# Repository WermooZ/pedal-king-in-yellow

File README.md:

# pedal-king-in-yellow

<br />This work is licensed under a <a rel="license" href="http://creativecommons.org/licenses/by-nc-sa/4.0/">Creative Commons Attribution-NonCommercial-ShareAlike 4.0 International License</a>.

Based on the **Exar Super Fuzz SF-02** traced by **VitaliiBobrov** at www.freestompboxes.org

https://www.freestompboxes.org/viewtopic.php?p=293456&hilit=exar#p293456

SF-2 is a fuzz pedal, handmade in Poland in 90s by not existing now Exar Electronix (Janusz Raczyk and Leszek Gruszka).

This version is modified a bit to my taste to improve clarity, tone and noise levels.

Project was assembled and tested - only thing that I messed up is a dual FREQ pot pins -> they are mirrored for one half of pot but it can be fixed by correct wiring so check the schematic first.

Please use Pieczarka logo on pedal enclosure if you want to design own graphics or 'Pieczarka' or 'PCZR' for short.

Project thread on FSB: https://www.freestompboxes.org/viewtopic.php?t=32591

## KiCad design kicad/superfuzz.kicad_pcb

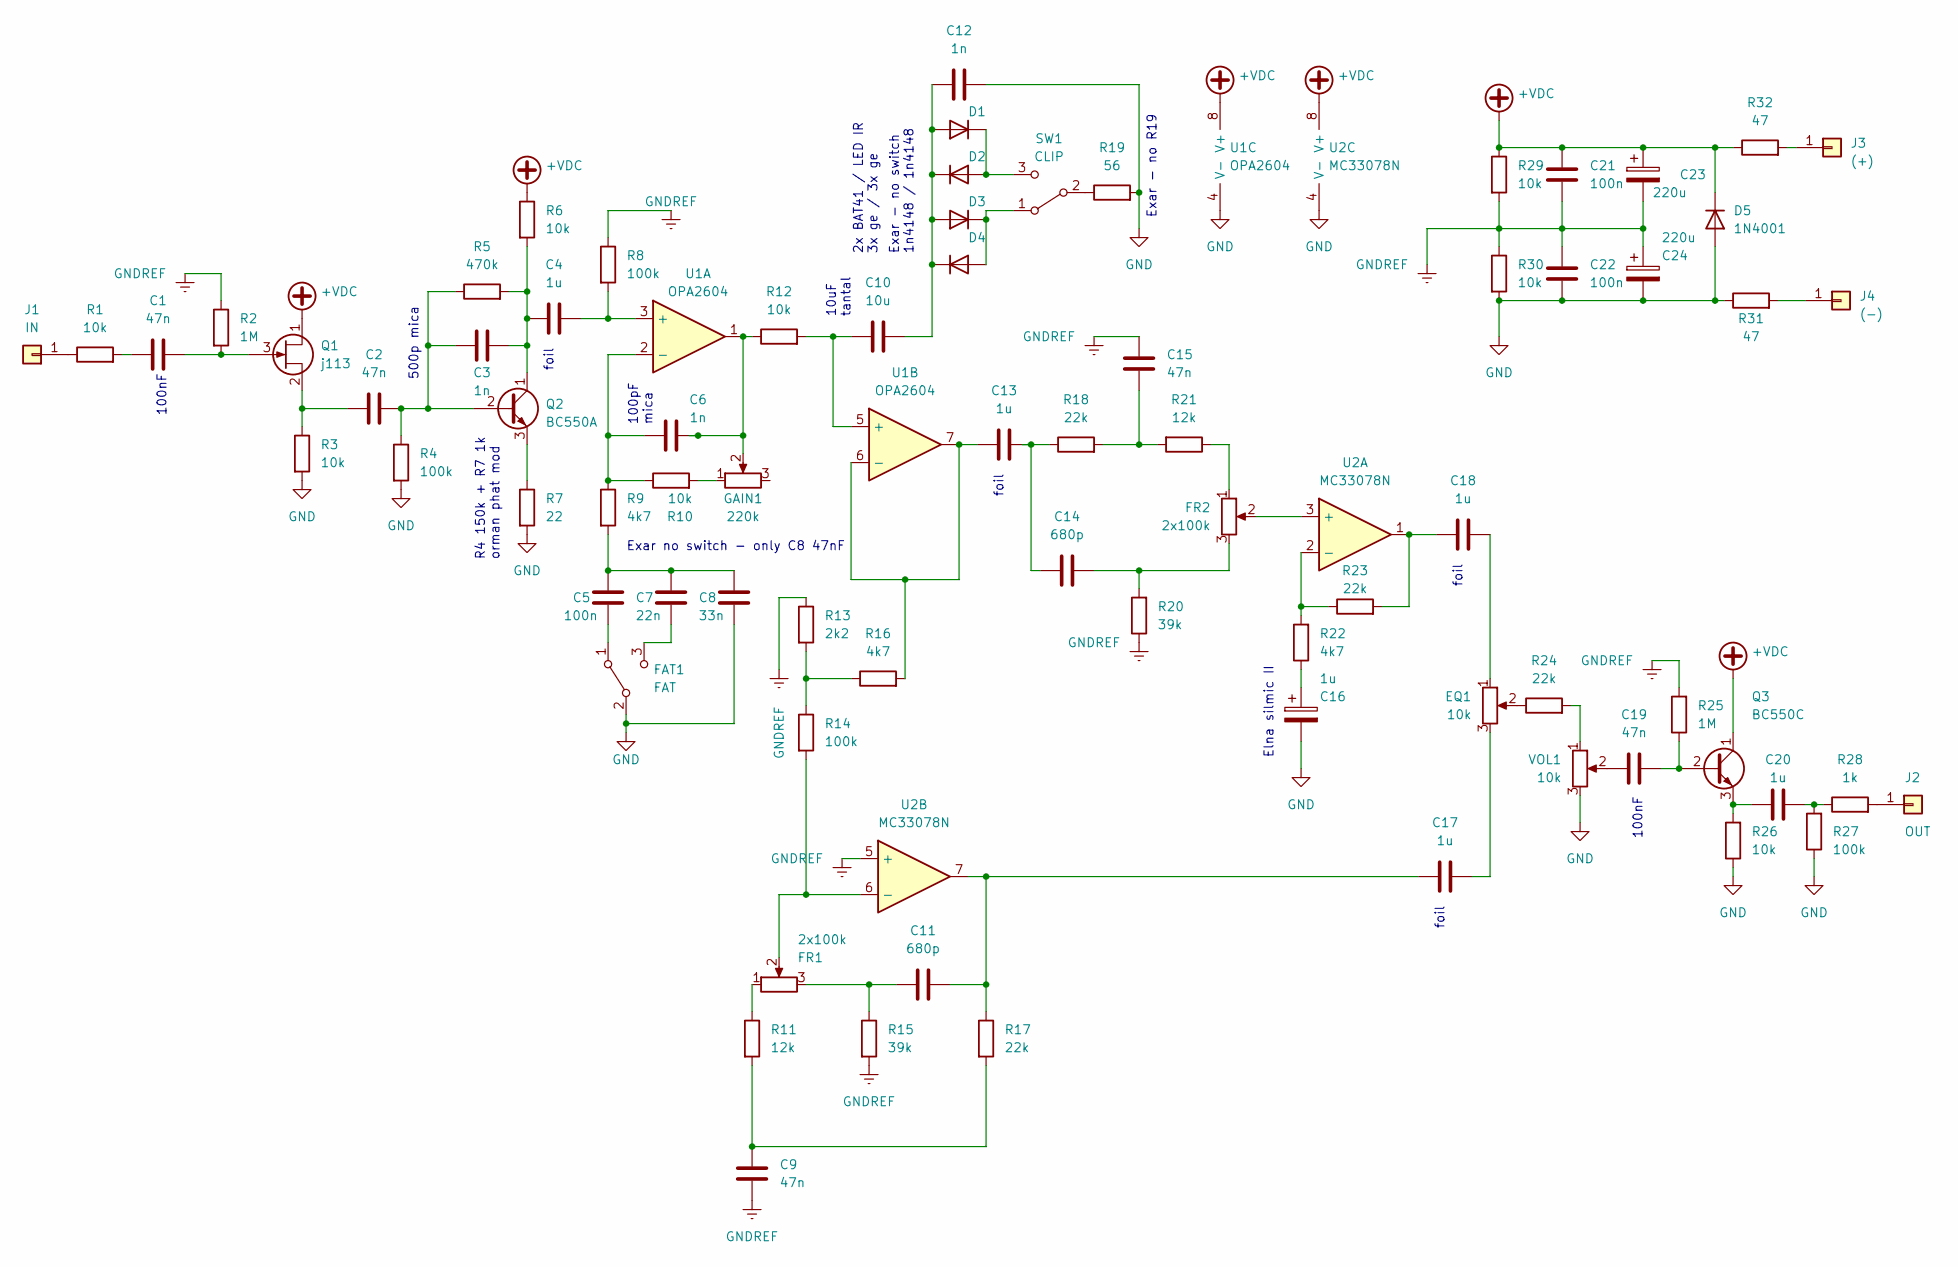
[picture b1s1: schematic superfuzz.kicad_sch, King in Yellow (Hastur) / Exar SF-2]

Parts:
C1, C2, C9, C15, C19: 47n; C_Rect_L13.0mm_W5.0mm_P10.00mm_FKS3_FKP3_MKS4
C3, C6, C12: 1n; C_Rect_L10.0mm_W5.0mm_P5.00mm_P7.50mm
C4, C13, C17, C18, C20: 1u; C_Rect_L7.2mm_W8.5mm_P5.00mm_FKP2_FKP2_MKS2_MKP2
C5: 100n; C_Rect_L10.0mm_W4.0mm_P7.50mm_MKS4
C7: 22n; C_Rect_L10.0mm_W4.0mm_P7.50mm_MKS4
C8: 33n; C_Rect_L10.0mm_W4.0mm_P7.50mm_MKS4
C10: 10u; C_Rect_L7.2mm_W8.5mm_P5.00mm_FKP2_FKP2_MKS2_MKP2
C11, C14: 680p; C_Rect_L7.2mm_W5.5mm_P5.00mm_FKS2_FKP2_MKS2_MKP2
C16: 1u; CP_Radial_D5.0mm_P2.50mm
C21, C22: 100n; C_Rect_L7.2mm_W5.5mm_P5.00mm_FKS2_FKP2_MKS2_MKP2
C23, C24: 220u; CP_Radial_D8.0mm_P5.00mm
D1, D2: 1N4148; D_DO-35_SOD27_P2.54mm_Vertical_AnodeUp
D3, D4: Ge; D_DO-35_SOD27_P2.54mm_Vertical_AnodeUp
D5: 1N4001; D_DO-41_SOD81_P3.81mm_Vertical_AnodeUp
EQ1: 10k; potek2
FAT1: FAT; potek2
FR1, FR2: 2x100k; potek2
GAIN1: 220k; potek2
J1: IN; Pin_D0.7mm_L6.5mm_W1.8mm_FlatFork
J2: OUT; Pin_D0.7mm_L6.5mm_W1.8mm_FlatFork
J3: (+); Pin_D0.7mm_L6.5mm_W1.8mm_FlatFork
J4: (-); Pin_D0.7mm_L6.5mm_W1.8mm_FlatFork
Q1: j113; TO-92_Inline_Wide
Q2: BC550A; TO-92_Inline
Q3: BC550C; TO-92_Inline
R1, R12, R26, R30: 10k; R_Axial_DIN0204_L3.6mm_D1.6mm_P2.54mm_Vertical
R2, R25: 1M; R_Axial_DIN0204_L3.6mm_D1.6mm_P7.62mm_Horizontal
R3, R6, R10, R29: 10k; R_Axial_DIN0204_L3.6mm_D1.6mm_P5.08mm_Horizontal
R4, R27: 100k; R_Axial_DIN0204_L3.6mm_D1.6mm_P5.08mm_Horizontal
R5: 470k; R_Axial_DIN0204_L3.6mm_D1.6mm_P5.08mm_Horizontal
R7: 22; R_Axial_DIN0204_L3.6mm_D1.6mm_P5.08mm_Horizontal
R8: 100k; R_Axial_DIN0204_L3.6mm_D1.6mm_P7.62mm_Horizontal
R9: 4k7; R_Axial_DIN0204_L3.6mm_D1.6mm_P5.08mm_Horizontal
R11: 12k; R_Axial_DIN0204_L3.6mm_D1.6mm_P5.08mm_Horizontal
R13: 2k2; R_Axial_DIN0204_L3.6mm_D1.6mm_P2.54mm_Vertical
R14: 100k; R_Axial_DIN0204_L3.6mm_D1.6mm_P2.54mm_Vertical
R15: 39k; R_Axial_DIN0204_L3.6mm_D1.6mm_P2.54mm_Vertical
R16, R22: 4k7; R_Axial_DIN0204_L3.6mm_D1.6mm_P2.54mm_Vertical
R17: 22k; R_Axial_DIN0204_L3.6mm_D1.6mm_P5.08mm_Horizontal
R18, R23, R24: 22k; R_Axial_DIN0204_L3.6mm_D1.6mm_P2.54mm_Vertical
R19: 56; R_Axial_DIN0204_L3.6mm_D1.6mm_P2.54mm_Vertical
R20: 39k; R_Axial_DIN0204_L3.6mm_D1.6mm_P5.08mm_Horizontal
R21: 12k; R_Axial_DIN0204_L3.6mm_D1.6mm_P2.54mm_Vertical
R28: 1k; R_Axial_DIN0204_L3.6mm_D1.6mm_P5.08mm_Horizontal
R31, R32: 47; R_Axial_DIN0204_L3.6mm_D1.6mm_P2.54mm_Vertical
SW1: CLIP; potek2
U1: OPA2604; DIP-8_W7.62mm_LongPads
U2: MC33078N; DIP-8_W7.62mm_LongPads
VOL1: 10k; potek2

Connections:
+VDC: C21.1, C23.1, D5.1 (K), Q1.1 (D), Q3.1 (C), R6.1, R29.1, R32.1, U1.8 (V+), U2.8 (V+)
GND: C8.2, C12.2, C16.2, C22.2, C24.2, D5.2 (A), FAT1.2 (B), R3.2, R4.2, R7.2, R19.2, R26.1, R27.1, R30.2, R31.1, U1.4 (V-), U2.4 (V-), VOL1.3
GNDREF: C9.1, C15.2, C21.2, C22.1, C23.2, C24.1, R2.1, R8.1, R13.1, R15.2, R20.1, R25.2, R29.2, R30.1, U2.5 (+)
unnamed: C1.1, R1.2
unnamed: C1.2, Q1.3 (G), R2.2
unnamed: C2.1, Q1.2 (S), R3.1
unnamed: C2.2, C3.1, Q2.2 (B), R4.1, R5.1
unnamed: C3.2, C4.1, Q2.1 (C), R5.2, R6.2
unnamed: C4.2, R8.2, U1.3 (+)
unnamed: C5.1, C7.1, C8.1, R9.2
unnamed: C5.2, FAT1.1 (A)
unnamed: C6.1, R9.1, R10.1, U1.2 (-)
unnamed: C6.2, GAIN1.2, R12.1, U1.1
unnamed: C7.2, FAT1.3 (C)
unnamed: C9.2, R11.2, R17.2
unnamed: C10.1, R12.2, U1.5 (+)
unnamed: C10.2, C12.1, D1.2 (A), D2.1 (K), D3.2 (A), D4.1 (K)
unnamed: C11.1, FR1.3, R15.1
unnamed: C11.2, C17.1, R17.1, U2.7
unnamed: C13.1, R16.2, U1.6 (-), U1.7
unnamed: C13.2, C14.1, R18.1
unnamed: C14.2, FR2.3, R20.2
unnamed: C15.1, R18.2, R21.2
unnamed: C16.1, R22.1
unnamed: C17.2, EQ1.3
unnamed: C18.1, R23.2, U2.1
unnamed: C18.2, EQ1.1
unnamed: C19.1, VOL1.2
unnamed: C19.2, Q3.2 (B), R25.1
unnamed: C20.1, Q3.3 (E), R26.2
unnamed: C20.2, R27.2, R28.1
unnamed: D1.1 (K), D2.2 (A), SW1.3 (C)
unnamed: D3.1 (K), D4.2 (A), SW1.1 (A)
unnamed: EQ1.2, R24.1
unnamed: FR1.1, R11.1
unnamed: FR1.2, R14.2, U2.6 (-)
unnamed: FR2.1, R21.1
unnamed: FR2.2, U2.3 (+)
unnamed: GAIN1.1, R10.2
unnamed: J1.1, R1.1
unnamed: J2.1, R28.2
unnamed: J3.1, R32.2
unnamed: J4.1, R31.2
unnamed: Q2.3 (E), R7.1
unnamed: R13.2, R14.1, R16.1
unnamed: R19.1, SW1.2 (B)
unnamed: R22.2, R23.1, U2.2 (-)
unnamed: R24.2, VOL1.1

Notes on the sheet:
Exar - no switch 1n4148 / 1n4148
100nF
Exar no switch - only C8 47nF
500p mica
foil
10uF tantal
Elna silmic II
Exar - no R19
100pF mica
R4 150k + R7 1k orman phat mod
2x BAT41 / LED IR 3x ge / 3x ge

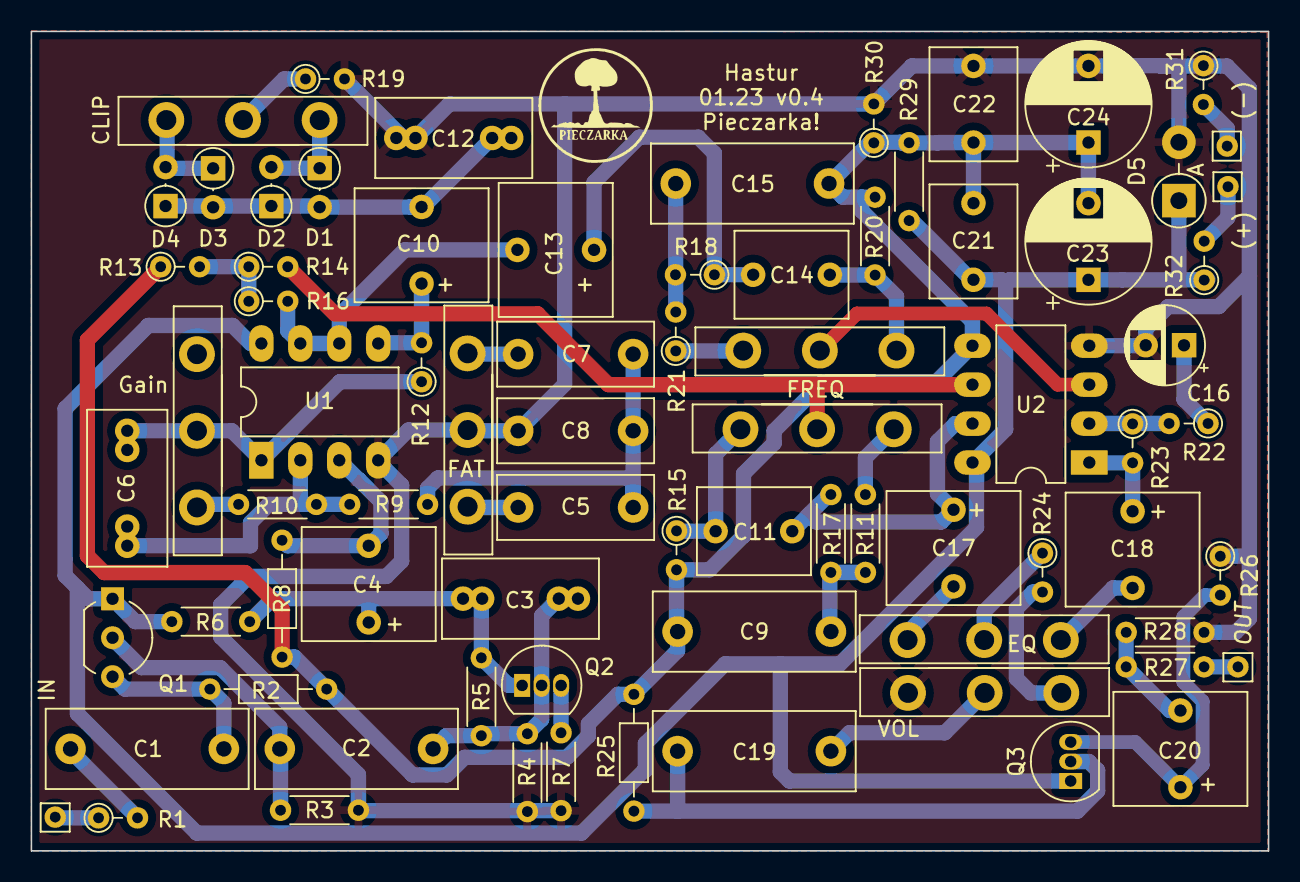
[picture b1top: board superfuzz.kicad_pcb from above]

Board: 2 copper layers, 80.7 x 53.5 mm, 77 parts (0 on the bottom side), 48 nets.

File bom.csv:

Source:,,,,,,
Date:,"sob, 28 sty 2023, 21:35:09",,,,,
Tool:,Eeschema (6.0.10),,,,,
Generator:,/usr/share/kicad/plugins/bom_csv_grouped_by_value_with_fp.py,,,,,
Component Count:,77,,,,,
Ref,Qnty,Value,Cmp name,Footprint,Description,Vendor
"C1, C2, C9, C15, C19, ",5,47n,C,Capacitor_THT:C_Rect_L13.0mm_W5.0mm_P10.00mm_FKS3_FKP3_MKS4,Unpolarized capacitor,
"C3, C6, C12, ",3,1n,C,Capacitor_THT:C_Rect_L10.0mm_W5.0mm_P5.00mm_P7.50mm,Unpolarized capacitor,
"C4, C13, C17, C18, C20, ",5,1u,C,Capacitor_THT:C_Rect_L7.2mm_W8.5mm_P5.00mm_FKP2_FKP2_MKS2_MKP2,Unpolarized capacitor,
"C5, ",1,82n,C,Capacitor_THT:C_Rect_L10.0mm_W4.0mm_P7.50mm_MKS4,Unpolarized capacitor,
"C7, C8, ",2,22n,C,Capacitor_THT:C_Rect_L10.0mm_W4.0mm_P7.50mm_MKS4,Unpolarized capacitor,
"C10, ",1,10u,C,Capacitor_THT:C_Rect_L7.2mm_W8.5mm_P5.00mm_FKP2_FKP2_MKS2_MKP2,Unpolarized capacitor,
"C11, C14, ",2,680p,C,Capacitor_THT:C_Rect_L7.2mm_W5.5mm_P5.00mm_FKS2_FKP2_MKS2_MKP2,Unpolarized capacitor,
"C16, ",1,1u,C_Polarized,Capacitor_THT:CP_Radial_D5.0mm_P2.50mm,Polarized capacitor,
"C21, C22, ",2,100n,C,Capacitor_THT:C_Rect_L7.2mm_W5.5mm_P5.00mm_FKS2_FKP2_MKS2_MKP2,Unpolarized capacitor,
"C23, C24, ",2,100u,C_Polarized,Capacitor_THT:CP_Radial_D8.0mm_P5.00mm,Polarized capacitor,
"D1, D2, ",2,1N4148,1N4148,Diode_THT:D_DO-35_SOD27_P2.54mm_Vertical_AnodeUp,"100V 0.15A standard switching diode, DO-35",
"D3, D4, ",2,Ge,1N4148,Diode_THT:D_DO-35_SOD27_P2.54mm_Vertical_AnodeUp,"100V 0.15A standard switching diode, DO-35",
"D5, ",1,1N4001,1N4001,Diode_THT:D_DO-41_SOD81_P3.81mm_Vertical_AnodeUp,"50V 1A General Purpose Rectifier Diode, DO-41",
"EQ1, ",1,10k,R_Potentiometer,varia:potek2,Potentiometer,
"FAT1, ",1,FAT,SW_SPDT,varia:potek2,"Switch, single pole double throw",
"FR1, ",1,R_Potentiometer,R_Potentiometer,varia:potek2,Potentiometer,
"FR2, ",1,100k,R_Potentiometer,varia:potek2,Potentiometer,
"GAIN1, ",1,220k,R_Potentiometer,varia:potek2,Potentiometer,
"J1, ",1,IN,Conn_01x01,Connector_Pin:Pin_D0.7mm_L6.5mm_W1.8mm_FlatFork,"Generic connector, single row, 01x01, script generated (kicad-library-utils/schlib/autogen/connector/)",
"J2, ",1,OUT,Conn_01x01,Connector_Pin:Pin_D0.7mm_L6.5mm_W1.8mm_FlatFork,"Generic connector, single row, 01x01, script generated (kicad-library-utils/schlib/autogen/connector/)",
"J3, J4, ",2,Conn_01x01,Conn_01x01,Connector_Pin:Pin_D0.7mm_L6.5mm_W1.8mm_FlatFork,"Generic connector, single row, 01x01, script generated (kicad-library-utils/schlib/autogen/connector/)",
"Q1, ",1,j113,Q_NJFET_DSG,Package_TO_SOT_THT:TO-92_Inline_Wide,"N-JFET transistor, drain/source/gate",
"Q2, Q3, ",2,BC550,BC550,Package_TO_SOT_THT:TO-92_Inline,"0.1A Ic, 45V Vce, Small Signal NPN Transistor, TO-92",
"R1, R12, R26, R30, ",4,10k,R,Resistor_THT:R_Axial_DIN0204_L3.6mm_D1.6mm_P2.54mm_Vertical,Resistor,
"R2, R25, ",2,1M,R,Resistor_THT:R_Axial_DIN0204_L3.6mm_D1.6mm_P7.62mm_Horizontal,Resistor,
"R3, R6, R10, R29, ",4,10k,R,Resistor_THT:R_Axial_DIN0204_L3.6mm_D1.6mm_P5.08mm_Horizontal,Resistor,
"R4, R27, ",2,100k,R,Resistor_THT:R_Axial_DIN0204_L3.6mm_D1.6mm_P5.08mm_Horizontal,Resistor,
"R5, ",1,470k,R,Resistor_THT:R_Axial_DIN0204_L3.6mm_D1.6mm_P5.08mm_Horizontal,Resistor,
"R7, ",1,22,R,Resistor_THT:R_Axial_DIN0204_L3.6mm_D1.6mm_P5.08mm_Horizontal,Resistor,
"R8, ",1,100k,R,Resistor_THT:R_Axial_DIN0204_L3.6mm_D1.6mm_P7.62mm_Horizontal,Resistor,
"R9, ",1,4k7,R,Resistor_THT:R_Axial_DIN0204_L3.6mm_D1.6mm_P5.08mm_Horizontal,Resistor,
"R11, ",1,12k,R,Resistor_THT:R_Axial_DIN0204_L3.6mm_D1.6mm_P5.08mm_Horizontal,Resistor,
"R13, ",1,2k2,R,Resistor_THT:R_Axial_DIN0204_L3.6mm_D1.6mm_P2.54mm_Vertical,Resistor,
"R14, ",1,100k,R,Resistor_THT:R_Axial_DIN0204_L3.6mm_D1.6mm_P2.54mm_Vertical,Resistor,
"R15, ",1,39k,R,Resistor_THT:R_Axial_DIN0204_L3.6mm_D1.6mm_P2.54mm_Vertical,Resistor,
"R16, R22, ",2,4k7,R,Resistor_THT:R_Axial_DIN0204_L3.6mm_D1.6mm_P2.54mm_Vertical,Resistor,
"R17, ",1,22k,R,Resistor_THT:R_Axial_DIN0204_L3.6mm_D1.6mm_P5.08mm_Horizontal,Resistor,
"R18, R23, R24, ",3,22k,R,Resistor_THT:R_Axial_DIN0204_L3.6mm_D1.6mm_P2.54mm_Vertical,Resistor,
"R19, ",1,56,R,Resistor_THT:R_Axial_DIN0204_L3.6mm_D1.6mm_P2.54mm_Vertical,Resistor,
"R20, ",1,39k,R,Resistor_THT:R_Axial_DIN0204_L3.6mm_D1.6mm_P5.08mm_Horizontal,Resistor,
"R21, ",1,12k,R,Resistor_THT:R_Axial_DIN0204_L3.6mm_D1.6mm_P2.54mm_Vertical,Resistor,
"R28, ",1,1k,R,Resistor_THT:R_Axial_DIN0204_L3.6mm_D1.6mm_P5.08mm_Horizontal,Resistor,
"R31, R32, ",2,47,R,Resistor_THT:R_Axial_DIN0204_L3.6mm_D1.6mm_P2.54mm_Vertical,Resistor,
"SW1, ",1,CLIP,SW_SPDT,varia:potek2,"Switch, single pole double throw",
"U1, U2, ",2,Opamp_Dual,Opamp_Dual,Package_DIP:DIP-8_W7.62mm_LongPads,Dual operational amplifier,
"VOL1, ",1,10k,R_Potentiometer,varia:potek2,Potentiometer,

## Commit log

2023-04-04 add files
2023-04-04 Add pieczarka logo
2023-05-06 Add cover designs
2023-05-07 Add kicad files and bom
